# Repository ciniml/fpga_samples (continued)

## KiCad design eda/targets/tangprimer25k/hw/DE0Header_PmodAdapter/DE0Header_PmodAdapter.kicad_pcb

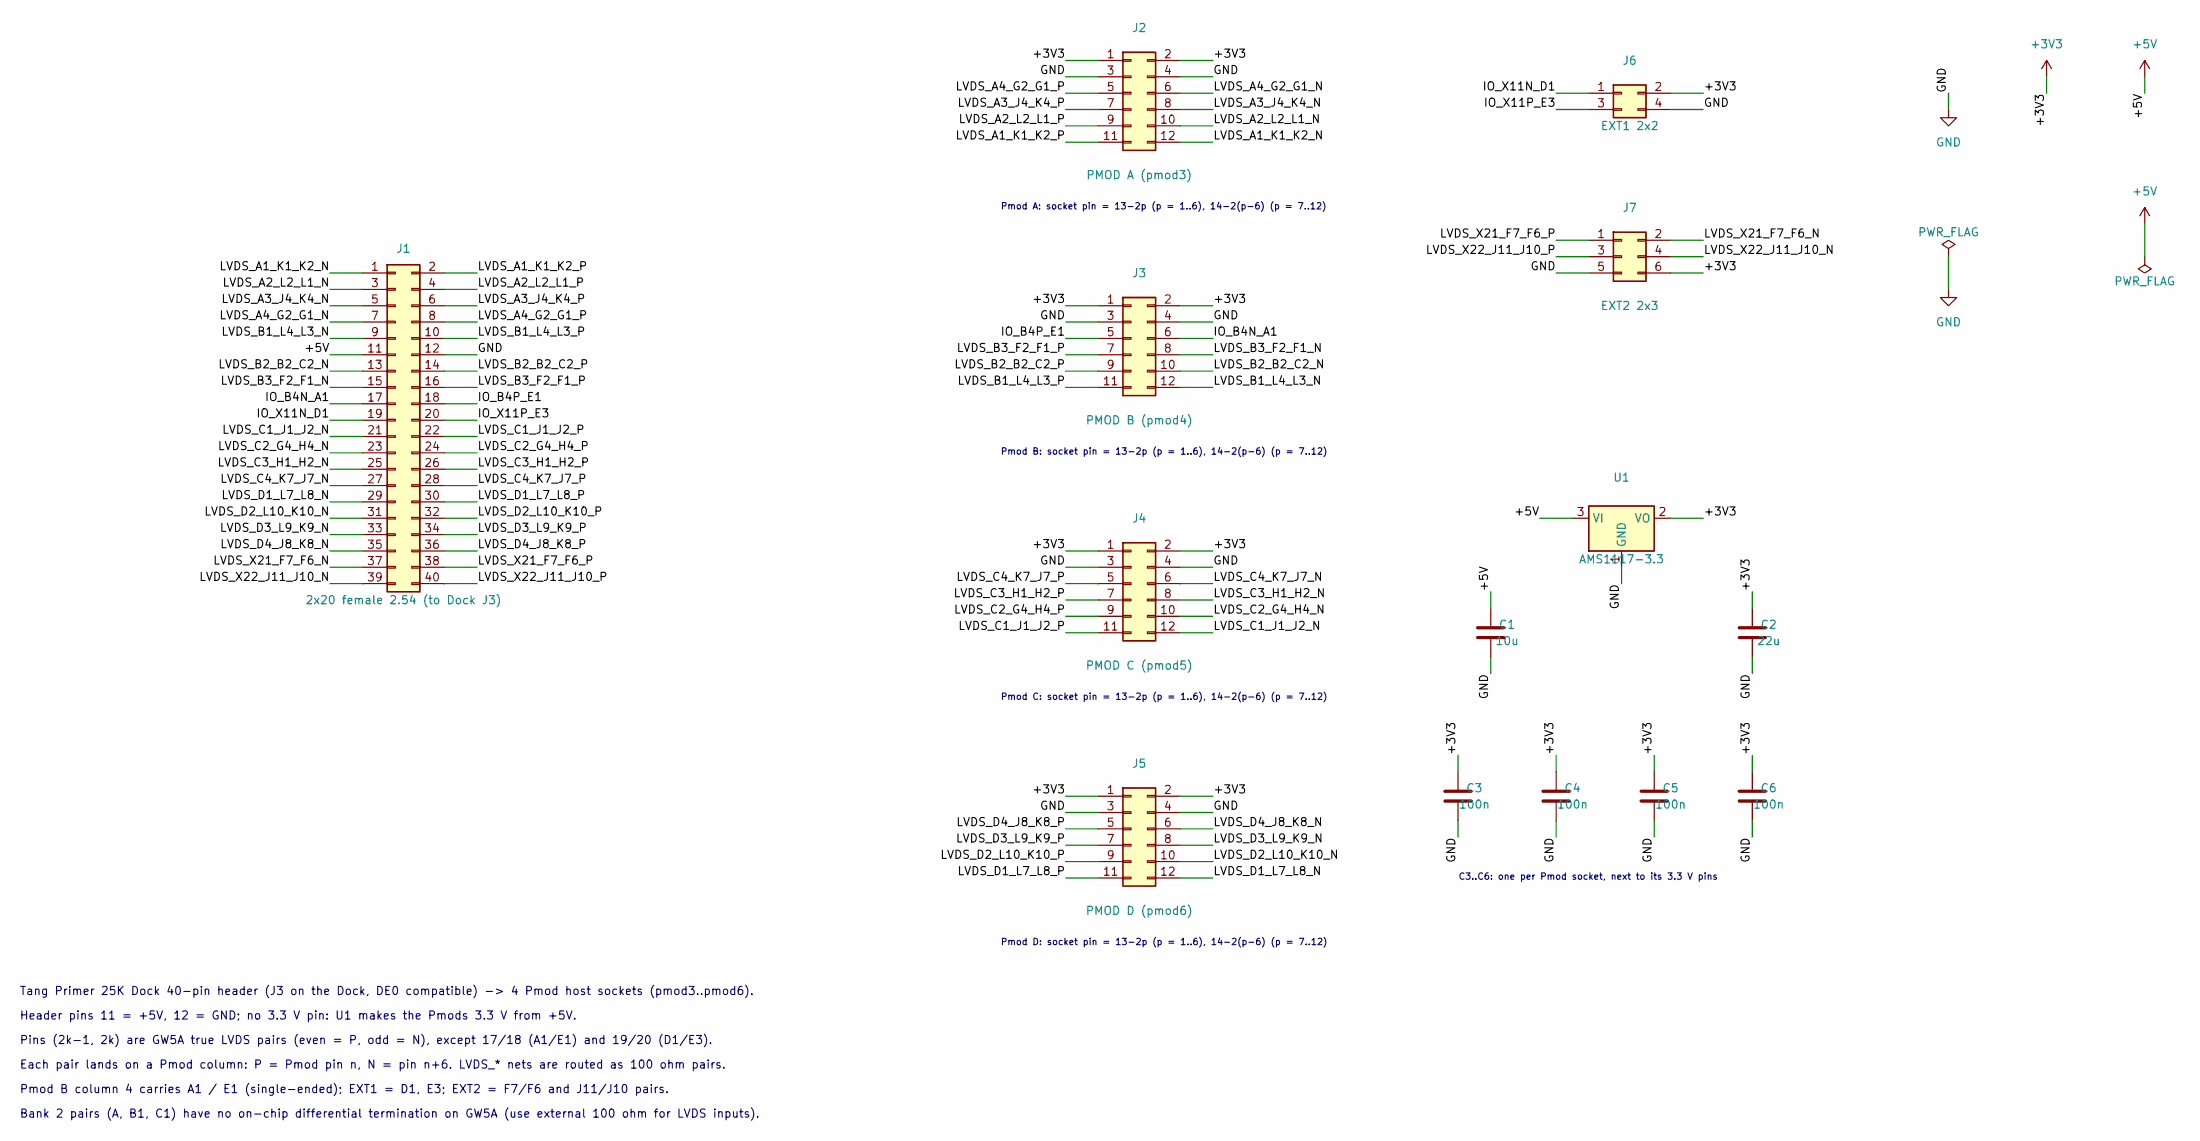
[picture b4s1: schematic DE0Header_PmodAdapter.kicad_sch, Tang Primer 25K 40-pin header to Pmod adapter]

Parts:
C1: 10u; C_0805_2012Metric; MPN Samsung CL21A106KAYNNNE; LCSC C15850
C2: 22u; C_0805_2012Metric; MPN Samsung CL21A226MAQNNNE; LCSC C45783
C3, C4, C5, C6: 100n; C_0402_1005Metric; MPN Samsung CL05B104KO5NNNC; LCSC C1525
J1: 2x20 female 2.54 (to Dock J3); PinSocket_2x20_P2.54mm_Vertical; MPN BOOMELE 2.54-2*20P; LCSC C5124634
J2: PMOD A (pmod3); PinSocket_2x06_P2.54mm_Horizontal; MPN Hong Cheng HC-PM254-8.5H-2x6PW; LCSC C22373932
J3: PMOD B (pmod4); PinSocket_2x06_P2.54mm_Horizontal; MPN Hong Cheng HC-PM254-8.5H-2x6PW; LCSC C22373932
J4: PMOD C (pmod5); PinSocket_2x06_P2.54mm_Horizontal; MPN Hong Cheng HC-PM254-8.5H-2x6PW; LCSC C22373932
J5: PMOD D (pmod6); PinSocket_2x06_P2.54mm_Horizontal; MPN Hong Cheng HC-PM254-8.5H-2x6PW; LCSC C22373932
J6: EXT1 2x2; PinHeader_2x02_P2.54mm_Vertical; MPN BOOMELE 2.54-2*2PPin; LCSC C66690
J7: EXT2 2x3; PinHeader_2x03_P2.54mm_Vertical; MPN BOOMELE 2.54-2*3PPin; LCSC C65114
U1: AMS1117-3.3; SOT-223-3_TabPin2; MPN AMS AMS1117-3.3; LCSC C6186

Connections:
+3V3: C2.1, C3.1, C4.1, C5.1, C6.1, J2.1, J2.2, J3.1, J3.2, J4.1, J4.2, J5.1, J5.2, J6.2, J7.6, U1.2 (VO)
+5V: C1.1, J1.11, U1.3 (VI)
/IO_B4N_A1: J1.17, J3.6
/IO_B4P_E1: J1.18, J3.5
/IO_X11N_D1: J1.19, J6.1
/IO_X11P_E3: J1.20, J6.3
/LVDS_A1_K1_K2_N: J1.1, J2.12
/LVDS_A1_K1_K2_P: J1.2, J2.11
/LVDS_A2_L2_L1_N: J1.3, J2.10
/LVDS_A2_L2_L1_P: J1.4, J2.9
/LVDS_A3_J4_K4_N: J1.5, J2.8
/LVDS_A3_J4_K4_P: J1.6, J2.7
/LVDS_A4_G2_G1_N: J1.7, J2.6
/LVDS_A4_G2_G1_P: J1.8, J2.5
/LVDS_B1_L4_L3_N: J1.9, J3.12
/LVDS_B1_L4_L3_P: J1.10, J3.11
/LVDS_B2_B2_C2_N: J1.13, J3.10
/LVDS_B2_B2_C2_P: J1.14, J3.9
/LVDS_B3_F2_F1_N: J1.15, J3.8
/LVDS_B3_F2_F1_P: J1.16, J3.7
/LVDS_C1_J1_J2_N: J1.21, J4.12
/LVDS_C1_J1_J2_P: J1.22, J4.11
/LVDS_C2_G4_H4_N: J1.23, J4.10
/LVDS_C2_G4_H4_P: J1.24, J4.9
/LVDS_C3_H1_H2_N: J1.25, J4.8
/LVDS_C3_H1_H2_P: J1.26, J4.7
/LVDS_C4_K7_J7_N: J1.27, J4.6
/LVDS_C4_K7_J7_P: J1.28, J4.5
/LVDS_D1_L7_L8_N: J1.29, J5.12
/LVDS_D1_L7_L8_P: J1.30, J5.11
/LVDS_D2_L10_K10_N: J1.31, J5.10
/LVDS_D2_L10_K10_P: J1.32, J5.9
/LVDS_D3_L9_K9_N: J1.33, J5.8
/LVDS_D3_L9_K9_P: J1.34, J5.7
/LVDS_D4_J8_K8_N: J1.35, J5.6
/LVDS_D4_J8_K8_P: J1.36, J5.5
/LVDS_X21_F7_F6_N: J1.37, J7.2
/LVDS_X21_F7_F6_P: J1.38, J7.1
/LVDS_X22_J11_J10_N: J1.39, J7.4
/LVDS_X22_J11_J10_P: J1.40, J7.3
GND: C1.2, C2.2, C3.2, C4.2, C5.2, C6.2, J1.12, J2.3, J2.4, J3.3, J3.4, J4.3, J4.4, J5.3, J5.4, J6.4, J7.5, U1.1 (GND)

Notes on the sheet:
Pmod A: socket pin = 13-2p (p = 1..6), 14-2(p-6) (p = 7..12)
Pmod B: socket pin = 13-2p (p = 1..6), 14-2(p-6) (p = 7..12)
Pmod C: socket pin = 13-2p (p = 1..6), 14-2(p-6) (p = 7..12)
Pmod D: socket pin = 13-2p (p = 1..6), 14-2(p-6) (p = 7..12)
C3..C6: one per Pmod socket, next to its 3.3 V pins
Tang Primer 25K Dock 40-pin header (J3 on the Dock, DE0 compatible) -> 4 Pmod host sockets (pmod3..pmod6).
Header pins 11 = +5V, 12 = GND; no 3.3 V pin: U1 makes the Pmods 3.3 V from +5V.
Pins (2k-1, 2k) are GW5A true LVDS pairs (even = P, odd = N), except 17/18 (A1/E1) and 19/20 (D1/E3).
Each pair lands on a Pmod column: P = Pmod pin n, N = pin n+6. LVDS_* nets are routed as 100 ohm pairs.
Pmod B column 4 carries A1 / E1 (single-ended); EXT1 = D1, E3; EXT2 = F7/F6 and J11/J10 pairs.
Bank 2 pairs (A, B1, C1) have no on-chip differential termination on GW5A (use external 100 ohm for LVDS inputs).

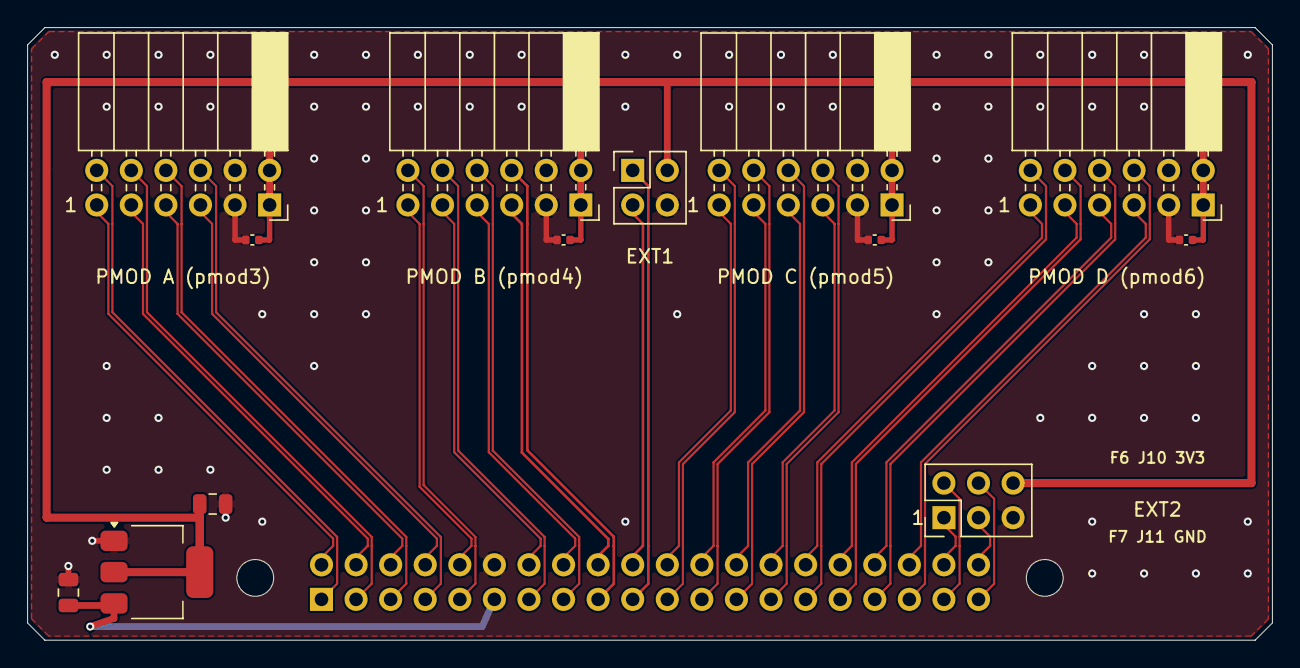
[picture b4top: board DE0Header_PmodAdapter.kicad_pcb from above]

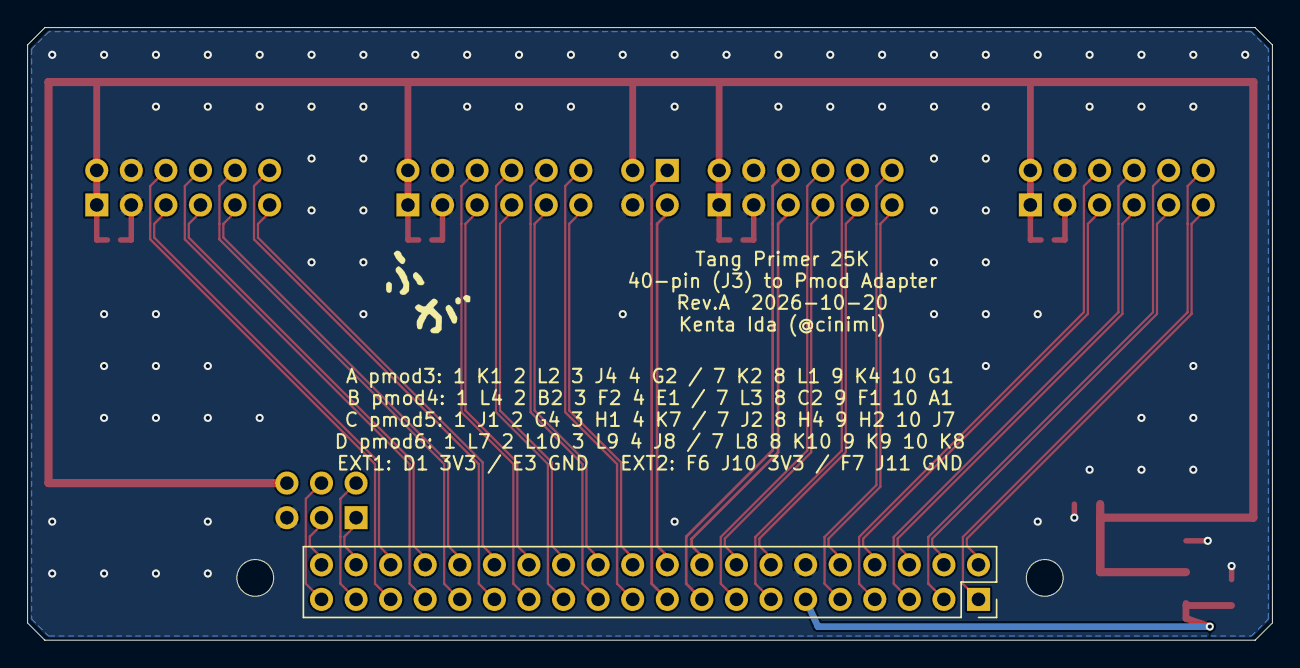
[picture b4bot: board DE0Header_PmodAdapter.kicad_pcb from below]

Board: 2 copper layers, 91.4 x 45.0 mm, 17 parts (2 on the bottom side), 41 nets.

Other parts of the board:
H1, H2: MountingHole_2.7mm_M2.5_ISO7380
LOGO1: logo

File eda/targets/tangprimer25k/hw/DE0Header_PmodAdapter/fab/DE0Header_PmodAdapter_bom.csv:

"Reference","Value","Footprint","QUANTITY","LCSC","MPN","Description"
"C1","10u","Capacitor_SMD:C_0805_2012Metric","1","C15850","Samsung CL21A106KAYNNNE","10 uF 25 V X5R 0805 (LDO input)"
"C2","22u","Capacitor_SMD:C_0805_2012Metric","1","C45783","Samsung CL21A226MAQNNNE","22 uF 25 V X5R 0805 (LDO output)"
"C3,C4,C5,C6","100n","Capacitor_SMD:C_0402_1005Metric","4","C1525","Samsung CL05B104KO5NNNC","100 nF 16 V X7R 0402 (Pmod 3.3 V)"
"J1","2x20 female 2.54 (to Dock J3)","Connector_PinSocket_2.54mm:PinSocket_2x20_P2.54mm_Vertical","1","C5124634","BOOMELE 2.54-2*20P","2x20 2.54 mm female socket, 8.5 mm, mounted on the bottom side"
"J2","PMOD A (pmod3)","Connector_PinSocket_2.54mm:PinSocket_2x06_P2.54mm_Horizontal","1","C22373932","Hong Cheng HC-PM254-8.5H-2x6PW","Pmod host: 2x6 2.54 mm right-angle female socket"
"J3","PMOD B (pmod4)","Connector_PinSocket_2.54mm:PinSocket_2x06_P2.54mm_Horizontal","1","C22373932","Hong Cheng HC-PM254-8.5H-2x6PW","Pmod host: 2x6 2.54 mm right-angle female socket"
"J4","PMOD C (pmod5)","Connector_PinSocket_2.54mm:PinSocket_2x06_P2.54mm_Horizontal","1","C22373932","Hong Cheng HC-PM254-8.5H-2x6PW","Pmod host: 2x6 2.54 mm right-angle female socket"
"J5","PMOD D (pmod6)","Connector_PinSocket_2.54mm:PinSocket_2x06_P2.54mm_Horizontal","1","C22373932","Hong Cheng HC-PM254-8.5H-2x6PW","Pmod host: 2x6 2.54 mm right-angle female socket"
"J6","EXT1 2x2","Connector_PinHeader_2.54mm:PinHeader_2x02_P2.54mm_Vertical","1","C66690","BOOMELE 2.54-2*2PPin","2x2 2.54 mm pin header"
"J7","EXT2 2x3","Connector_PinHeader_2.54mm:PinHeader_2x03_P2.54mm_Vertical","1","C65114","BOOMELE 2.54-2*3PPin","2x3 2.54 mm pin header"
"U1","AMS1117-3.3","Package_TO_SOT_SMD:SOT-223-3_TabPin2","1","C6186","AMS AMS1117-3.3","3.3 V 1 A LDO (5 V from the header pin 11)"

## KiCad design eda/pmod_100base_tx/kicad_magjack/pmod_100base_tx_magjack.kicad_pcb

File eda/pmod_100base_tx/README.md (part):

# Pmod 100BASE-TX 直結 PHY 基板 — 設計検討

外付け PHY チップを使わず、Tang Primer 25K (GW5A-25) の I/O だけで 100BASE-TX を送受信するための
Pmod 基板案。**パルストランスも使わず**、コンデンサ結合 (transformerless) で RJ45 に直結する。
受信は EasyCDR / USB HS と同じブラインド・オーバーサンプリング CDR (`rtl/oscdr` の `OsCdr`)。
RTL は `rtl/eth100_phy` (Veryl)。

状態: **机上検討 + RTL シミュレーション合格 + 実機用ビットストリーム生成済み** (KiCad 10 データ: トランスレス版 `kicad/`、MagJack 版 `kicad_magjack/`。実機未検証)。

## 1. 要求と方針

| 項目 | 内容 |
|---|---|
| 規格 | 100BASE-TX (4B5B + 11bit スクランブラ + MLT-3、125 Mbaud)。全二重。10BASE-T は非対象 (FLP の送受信のみ) |
| 役割 | MDI (NIC 側): **TX = RJ45 1/2、RX = 3/6**。相手はスイッチ / Auto-MDIX の PC |
| 絶縁 | トランスレス版はなし (**相手側にトランスがある前提**、PoE 非対応)。MagJack 版 (§3.5) は 1500V 絶縁 |
| オートネゴ | FLP を自前生成 / 復号し 100BASE-TX FD を広告。出さないと相手はパラレル検出で **100M 半二重**に落ちる |
| Pmod | **1 ポート** (信号 8 本 = 差動対 4)。3.3V バンク。Tang Primer 25K の csv `pmod0` を想定 |
| ケーブル | まず数 m。イコライザなしの 2 値コンパレータなので 100m は保証しない (§6) |

## 2. 原理

### 2.1 MLT-3 を比較器 2 個で受ける

差動受信電圧 `v` (+1/0/−1 V 名目) を、しきい値 `+th` と `−th` の 2 つの LVDS 入力 (比較器) で判定する。

| レベル | A = (v > +th) | B = (v > −th) | c = A ^ B |
|---|---|---|---|
| +1 | 1 | 1 | 0 |
| 0 | 0 | 1 | 1 |
| −1 | 0 | 0 | 0 |

MLT-3 はスクランブル後のビット 1 ごとに 0→+→0→−→0 と 1 段動くので、**どの遷移でも A か B の
どちらか一方だけが反転する**。よって `c = A ^ B` (= |v| < th の窓比較) は **NRZI 波形そのもの**になり、
`c[n] ^ c[n−1]` がスクランブル後のビット。CDR はこの `c` 1 本に対して OsCdr を回せばよい
(A/B はサンプル単位で XOR してから OsCdr に入れる)。A/B 個別のサンプルはアイスキャン・FLP 検出に使う。

### 2.2 サンプリング

- IDES4 ×2 (A, B)、FCLK 250 MHz DDR / PCLK 125 MHz = **500 MS/s、4 サンプル/シンボル**
  (EasyCDR 1 Gbps と同じ OSR=4。USB HS の OSIDES32 3.84 GS/s よりずっと楽)
- OsCdr `SAMPLES=4, OSR=4, IIR=4, FRAC=4, HYST=16`: 1 ワード = 1 シンボル、`nbits` は 0/1/2
  (プレシオクロナスのスリップ吸収)
- 送信もシンボルクロック 125 MHz。送受信とも同じ 125 MHz ドメインで、受信側の周波数差は
  「1 クロックに 0〜2 ビット」として PCS が吸収する (FIFO 不要)
- **8 サンプル/シンボル (1 GS/s, OSR=8) は不可**: OsCdr の追従判定は「データ点の隣のクラス (d, d+2) に
  エッジが来たら 1 ステップ」で OSR=4 前提。OSR=8 ではエッジが d±4 にあり、アイがほぼ閉じるまで動かない
  (USB HS はパケット毎の再捕捉で回避していた)。シミュレーションで ±200 ppm でも片方向が全滅した
- **OsCdr に `FRAC` (小数ビット) を追加**: 1 ワード 1 シンボルだとエッジは高々 1 個/ワードで、
  整数の IIR 減衰 `acc >> IIR` が 0 に丸められ全クラスが飽和する。`FRAC=0` (既定) は従来と同一論理で、
  既存 oscdr テスト 17 本は通過

## 3. 回路

### 3.1 ブロック図

```
 RJ45 (磁気なし)                    Pmod 基板                                         FPGA (Pmod)
                                                    ┌─ Rs 62Ω ─ TX_P ──────────────── pin4  LVCMOS33 DRIVE=16
 1 TD+ ──┬─ TVS ── C 0.1µF/100V ──┬─ Cr 47pF ─┤     ├─ Rp 120Ω ─ GND
 2 TD− ──┼─ TVS ── C 0.1µF/100V ──┼─ Cr 47pF ─┤     ├─ Rs 62Ω ─ TX_N ──────────────── pin10 LVCMOS33 DRIVE=16
         │                     (CMC 任意, 0Ω 実装)   └─ Rp 120Ω ─ GND

 3 RD+ ──┬─ TVS ──┬─ 49.9Ω ─┬─ 49.9Ω ─┬─ RD−                      (100Ω 終端、中点 Ct 10nF/100V → GND)
 6 RD− ──┘        │         Ct        │
                  ├─ Ca 0.1µF ── A_P ──┬─ Rb 2.2k ─ VB ────────── pin1  比較器 A  P
                  │                                         ┌──── pin7          A  N
                  │             RD− ── Ca 0.1µF ── A_N ─────┴─ Rb 2.2k ─ VTH_A
                  ├─ Ca 0.1µF ── B_P ──┬─ Rb 2.2k ─ VTH_B ──── pin2  比較器 B  P
                                RD− ── Ca 0.1µF ── B_N ──┬─ Rb 2.2k ─ VB ──── pin8  B  N

 VB    = 3.3V ─ 270Ω ─┬─ 180Ω ─ GND   (1.32V、10µF + 0.1µF)
 VTH_A = PWM_A(pin3) ─ 3.3k ─┬─ 1k ─ VB    (1µF → GND)
 VTH_B = PWM_B(pin9) ─ 3.3k ─┬─ 1k ─ VB    (1µF → GND)
 4/5, 7/8 (未使用対): 各対を 75Ω ×2 で中点 → 1nF/2kV → GND (Bob Smith 相当、任意)
```

### 3.2 受信: しきい値

- 比較器 A: `A_P = VB + v+`、`A_N = VTH_A + v−` → **A = 1 ⇔ v > (VTH_A − VB)**
- 比較器 B: `B_P = VTH_B + v+`、`B_N = VB + v−` → **B = 1 ⇔ v > −(VTH_B − VB)**
- つまり 2 本の PWM はどちらも「VB より上」に置けば ±th になる。名目 `VTH_A = VTH_B = VB + 0.5V` (短ケーブル)
- PWM → しきい値: `VTH − VB = (D × 3.3V − VB) × 1k / 4.3k` = **−0.31 V (D=0) 〜 +0.46 V (D=1)**。
  10bit PWM (125 MHz / 1024 = 122 kHz) で ~0.75 mV/LSB、RC τ ≈ 0.77 ms
  - 0.5V に少し届かないが、受信端で 1V 振幅が残るのは極短ケーブルのみ。長くするほど最適点は下がる。
    上を広げたいときは 3.3k → 2.7k
- 2 本独立なので、**差 (VTH_A − VTH_B) でベースラインの補正**、**和でしきい値の大きさ**を動かせる。
  さらに CDR を凍結したまま掃引すれば振幅方向のアイスキャンになる (OsCdr の位相固定と組み合わせて 2 次元)
- 各比較器入力は 0.1µF + 2.2k の HPF (720 Hz)。終端 (100Ω) とは別ノードにして DC オフセットを個別に与える。
  2.2k ×4 のタップ負荷は終端に対して無視できる
- 内蔵終端は使わない (`DIFF_RESISTOR=OFF`)。LVDS25 入力の電圧範囲は VB±1V ≒ 0.3〜2.3V
- ベースラインワンダ: 主因は**相手側トランスの低域遮断** (~20 kHz) で、こちらのコンデンサの有無に関係なく来る。
  通常のスクランブル済みデータなら数十 mV 程度で、±0.5V のしきい値に対して余裕がある。
  意図的な killer packet には弱い (§6)

### 3.3 送信: LVCMOS33 2 本で 3 値

| TX_P | TX_N | 出力 |
|---|---|---|
| 1 | 0 | +1 V |
| 0 | 1 | −1 V |
| 0 | 0 | 0 |

- 片側のテブナン等価を **2V / 50Ω** にすると 100Ω 負荷で ±1V。ピン出力抵抗を ~20Ω (DRIVE=16) と見て
  Rs = 62Ω (+20Ω)、Rp = 120Ω: V_th = 3.3 × 120/202 = 1.96V、R_th = 48.7Ω → **差動 0.99V**。
  規格は 0.95〜1.05V なので実測で Rs を合わせる (USB HS も DRIVE で振幅が大きく変わった)
- 立ち上がり 3〜5 ns (規格): ノードのインピーダンス ~25Ω (50Ω ‖ 線路 50Ω) に Cr ≈ 47pF で ~2.6 ns。
  スコープで合わせる
- 2 本で作るので**同相電圧が 0 ↔ 1V で段差状に動く** (±レベル時のみ片方が H)。直列コンデンサの後は過渡分だけが
  ケーブルに乗り、相手のトランスとコモンモードチョークで落ちる。EMI 対策に CMC (例: 0805 の 90Ω 級) の
  フットプリントを用意し、初版は 0Ω 実装
- 消費: H 側ピン ~16 mA。平均 1 本未満
- FLP (オートネゴのリンクパルス) も同じ回路で +1V × 100ns を出す。10BASE-T の規格振幅 (2.2〜2.8V) より小さいが、
  相手の受信スケルチ (~0.3〜0.6V) は超える見込み (§6 リスク)

### 3.4 保護・PoE (トランスレス版)

- RJ45 直近に 4 ライン低容量 TVS アレイ (TX 2 + RX 2)。**双方向品** (TPD4E02B04): 線路側に DC の基準が無いので、
  単方向品だと受信 FLP の負側で整流が起きる
- 線路側ノード (TD±, RD±) は直列 C と TVS のリークでしか DC が決まらないので、**1 MΩ の放電抵抗**で GND に落とす
- **PoE 非対応**。当初「線路側 C を 100V 耐圧にすればパッシブ PoE (24〜57V の同相電圧) に耐える」としていたが誤り:
  ≤1 pF 級 TVS は数 V でクランプするため導通・破損する。IEEE PoE (802.3af/at) は 25kΩ シグネチャ検出が
  通らないので給電されないが、パッシブ PoE のポートには**つながない** (シルクに明記)
- **相手機器もトランスレスの場合**は GND 電位差がそのまま乗る → 対象外

### 3.5 MagJack 版 (`kicad_magjack/`)

トランスレス版の不安要素 (PoE、線路側の DC 浮き、同相段差、相手もトランスレスのとき) をまとめて消す実用版。
FPGA 側の回路・ピン割り当て・RTL は共通で、RJ45 周りだけが違う。トランスは 1:1 なので FLP 振幅 (1V) と
ベースラインワンダ (主因は相手側トランス) は変わらない。

```
 Pmod ── Rs/Rp/Cr ── C (DC 阻止、必須) ── TD± ┐            ┌─ RJ45 1/2
                                               ├ HR911105A ┤  (1:1 + CT、CMC、Bob Smith 内蔵)
 Pmod ── 比較器タップ ── 100Ω 終端 ────── RD± ┘            └─ RJ45 3/6
 TCT / RCT (PHY 側センタータップ) ── 0.1µF ── GND   (3.3V に吊らない: 送信は電圧駆動)
 低容量 TVS (双方向 TPD4E02B04) は PHY 側 (トランスと回路の間)
```

- **TX の直列 C は必須**: 2 本で 3 値を作るので ± 状態では TX_P/TX_N 間に DC が掛かる。巻線の DCR は ~1Ω で、
  C が無いと抵抗網経由の DC 電流で磁気飽和する。絶縁側なので耐圧は 16〜50V でよい
- センタータップは AC 接地のみ。電流出力型 PHY 用のリファレンス回路 (CT を電源へ) は流用しない。
  そのため PHY 側も DC 的には浮いている (CT も終端中点もコンデンサ経由) → TVS は双方向品。
  DC を固定したければ TCT/RCT → GND に 1 MΩ (未実装)
- 基板: 2 層 20.32 × 52.0 mm、HR911105A (KiCad 10 stock の `RJ45_Hanrun_HR911105A_Horizontal`)。
  ピン 1 TD+ / 2 TD− / 3 RD+ / 4 TCT / 5 RCT / 6 RD− / 8 内蔵 Bob Smith → GND、LED 未使用。
  開口の向きと内蔵 1000pF の耐圧はデータシートで要確認 (stock に 3D モデルなし)
- PoE: 給電機器 (PSE) ではない。パッシブ PoE の同相電圧はトランスのセンタータップと内蔵 Bob Smith 側で受け、
  回路側は絶縁される

#### JLCPCB 実装用の部品 (LCSC 在庫・単価は 2026-10-19 時点)

`kicad_magjack/tools/outputs.sh` が `out/jlc/` に gerber zip、BOM、CPL を出す (CPL は gerber と同じ絶対座標)。
部品は `tools/design.py` の `lcsc` が正。値・MPN だけ変えるときは `gen_sch.py` → `update_fields.py`
(配線を残したまま PCB のフィールドだけ更新。`gen_pcb.py` は配線が消える)。

| Ref | 部品 | LCSC | JLC 区分 | 備考 |
|---|---|---|---|---|
| R1, R2 (Rs) | 62Ω 1% 0402 FOJAN FRC0402F62R0TS | C2909376 | Extended | 62Ω は Basic に無い。実機で振幅合わせに交換する前提 |
| R3, R4 | 120Ω 1% 0402 | C25079 | Basic | |
| R7, R8 | 49.9Ω 1% 0402 | C25120 | Basic | |
| R9–R12 | 2.2kΩ 1% 0402 | C25879 | Basic | |
| R13 / R14 (VB) | **330Ω / 220Ω** 1% 0402 | C25104 / C25091 | Basic | トランスレス版の 270/180 は両方 Extended なので変更。同じ 1.32V、出力抵抗 132Ω、5.9mA |
| R15, R17 | 3.3kΩ 1% 0402 | C25890 | Basic | 2.7k (C25885、Extended) でしきい値範囲が広がる |
| R16, R18 | 1kΩ 1% 0402 | C11702 | Basic | |
| C1, C2 (Cr) | 47pF C0G 50V 0402 | C1567 | Basic | |
| C3, C4, C6–C9 | 0.1µF X7R 50V 0603 | C14663 | Basic | TX DC 阻止 / Ca タップ |
| C5 | 10nF X7R 50V 0402 | C15195 | Basic | |
| C10, C14 | 10µF X5R 10V 0603 | C19702 | Basic | |
| C11, C15–C18 | 0.1µF X7R 50V 0402 | C307331 | Basic | C1525 (16V) は LCSC 在庫 0 だったため |
| C12, C13 | 1µF X5R 25V 0402 | C52923 | Basic | |
| U1 | TI TPD4E02B04DQAR (USON-10) | C106794 | Extended | 在庫 3.7 万。互換品 TECH PUBLIC TPD4E02B04DQAR-TP (C2841426) は容量の規定が違うので使わない |
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
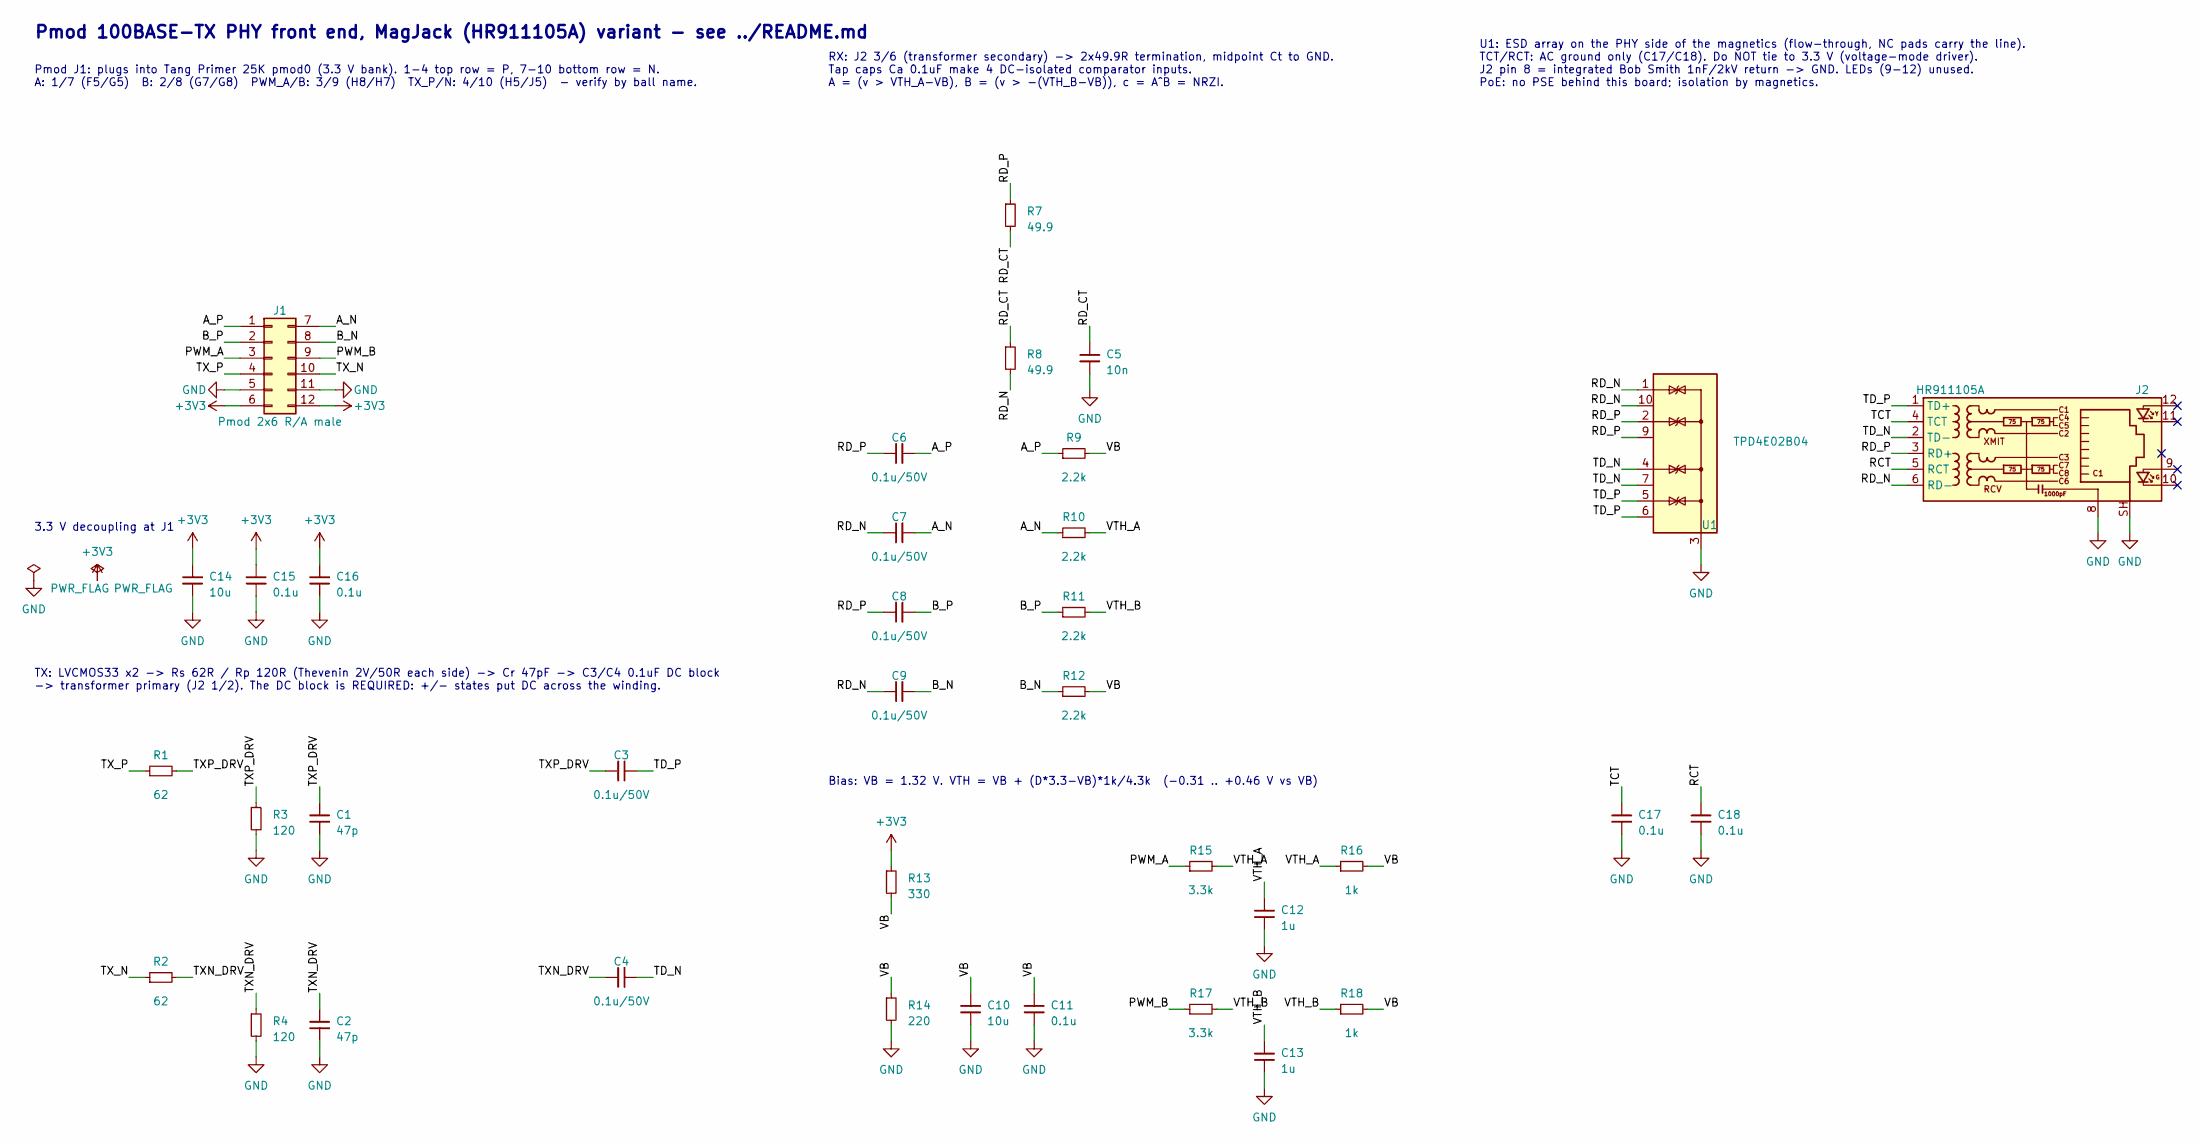
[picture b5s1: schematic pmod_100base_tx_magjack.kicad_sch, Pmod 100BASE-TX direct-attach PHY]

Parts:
C1, C2: 47p; C_0402_1005Metric; MPN 0402CG470J500NT; LCSC C1567
C3, C4, C6, C7, C8, C9: 0.1u/50V; C_0603_1608Metric; MPN CC0603KRX7R9BB104; LCSC C14663
C5: 10n; C_0402_1005Metric; MPN CL05B103KB5NNNC; LCSC C15195
C10, C14: 10u; C_0603_1608Metric; MPN CL10A106KP8NNNC; LCSC C19702
C11, C15, C16, C17, C18: 0.1u; C_0402_1005Metric; MPN CL05B104KB54PNC; LCSC C307331
C12, C13: 1u; C_0402_1005Metric; MPN CL05A105KA5NQNC; LCSC C52923
J1: Pmod 2x6 R/A male; Pmod_Peripheral_2x06_P2.54mm_Horizontal; MPN TSW-106-08-G-D-RA
J2: HR911105A; RJ45_Hanrun_HR911105A_Horizontal; MPN HR911105A; LCSC C12074
R1, R2: 62; R_0402_1005Metric; MPN FRC0402F62R0TS; LCSC C2909376
R3, R4: 120; R_0402_1005Metric; MPN 0402WGF1200TCE; LCSC C25079
R7, R8: 49.9; R_0402_1005Metric; MPN 0402WGF499JTCE; LCSC C25120
R9, R10, R11, R12: 2.2k; R_0402_1005Metric; MPN 0402WGF2201TCE; LCSC C25879
R13: 330; R_0402_1005Metric; MPN 0402WGF3300TCE; LCSC C25104
R14: 220; R_0402_1005Metric; MPN 0402WGF2200TCE; LCSC C25091
R15, R17: 3.3k; R_0402_1005Metric; MPN 0402WGF3301TCE; LCSC C25890
R16, R18: 1k; R_0402_1005Metric; MPN 0402WGF1001TCE; LCSC C11702
U1: TPD4E02B04; USON-10_2.5x1.0mm_P0.5mm; MPN TPD4E02B04DQAR; LCSC C106794

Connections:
+3V3: C14.1, C15.1, C16.1, J1.6, J1.12, R13.1
/A_N: C7.2, J1.7, R10.1
/A_P: C6.2, J1.1, R9.1
/B_N: C9.2, J1.8, R12.1
/B_P: C8.2, J1.2, R11.1
/PWM_A: J1.3, R15.1
/PWM_B: J1.9, R17.1
/RCT: C18.1, J2.5 (RCT)
/RD_CT: C5.1, R7.2, R8.1
/RD_N: C7.1, C9.1, J2.6 (RD-), R8.2, U1.1 (IO1), U1.10 (NC)
/RD_P: C6.1, C8.1, J2.3 (RD+), R7.1, U1.2 (IO2), U1.9 (NC)
/TCT: C17.1, J2.4 (TCT)
/TD_N: C4.2, J2.2 (TD-), U1.4 (IO3), U1.7 (NC)
/TD_P: C3.2, J2.1 (TD+), U1.5 (IO4), U1.6 (NC)
/TXN_DRV: C2.1, C4.1, R2.2, R4.1
/TXP_DRV: C1.1, C3.1, R1.2, R3.1
/TX_N: J1.10, R2.1
/TX_P: J1.4, R1.1
/VB: C10.1, C11.1, R9.2, R12.2, R13.2, R14.1, R16.2, R18.2
/VTH_A: C12.1, R10.2, R15.2, R16.1
/VTH_B: C13.1, R11.2, R17.2, R18.1
GND: C1.2, C2.2, C5.2, C10.2, C11.2, C12.2, C13.2, C14.2, C15.2, C16.2, C17.2, C18.2, J1.5, J1.11, J2.8, J2.SH, R3.2, R4.2, R14.2, U1.3 (G), U1.8 (G)

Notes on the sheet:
Pmod 100BASE-TX PHY front end, MagJack (HR911105A) variant - see ../README.md
Pmod J1: plugs into Tang Primer 25K pmod0 (3.3 V bank). 1-4 top row = P, 7-10 bottom row = N. A: 1/7 (F5/G5) B: 2/8 (G7/G8) PWM_A/B: 3/9 (H8/H7) TX_P/N: 4/10 (H5/J5) - verify by ball name.
TX: LVCMOS33 x2 -> Rs 62R / Rp 120R (Thevenin 2V/50R each side) -> Cr 47pF -> C3/C4 0.1uF DC block -> transformer primary (J2 1/2). The DC block is REQUIRED: +/- states put DC across the winding.
RX: J2 3/6 (transformer secondary) -> 2x49.9R termination, midpoint Ct to GND. Tap caps Ca 0.1uF make 4 DC-isolated comparator inputs. A = (v > VTH_A-VB), B = (v > -(VTH_B-VB)), c = A^B = NRZI.
Bias: VB = 1.32 V. VTH = VB + (D*3.3-VB)*1k/4.3k (-0.31 .. +0.46 V vs VB)
U1: ESD array on the PHY side of the magnetics (flow-through, NC pads carry the line). TCT/RCT: AC ground only (C17/C18). Do NOT tie to 3.3 V (voltage-mode driver). J2 pin 8 = integrated Bob Smith 1nF/2kV return -> GND. LEDs (9-12) unused. PoE: no PSE behind this board; isolation by magnetics.
3.3 V decoupling at J1

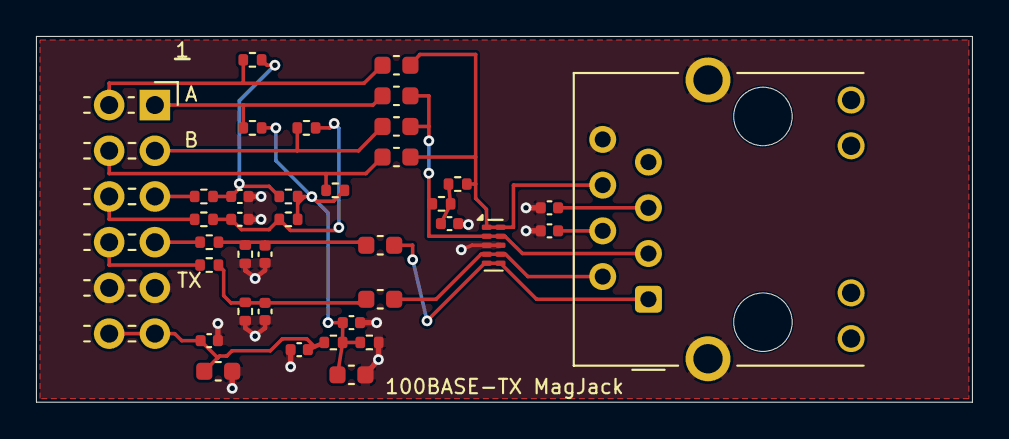
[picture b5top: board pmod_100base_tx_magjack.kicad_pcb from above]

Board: 2 copper layers, 52.0 x 20.3 mm, 38 parts (1 on the bottom side), 22 nets.

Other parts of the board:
LOGO1: Logo_Open_Hardware_Small; logo

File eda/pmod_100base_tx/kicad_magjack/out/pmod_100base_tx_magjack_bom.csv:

"Refs","Value","Footprint","MPN","Manufacturer","LCSC","Description","Qty","DNP"
"C1,C2","47p","Capacitor_SMD:C_0402_1005Metric","0402CG470J500NT","FH","C1567","Cr C0G 50V, edge rate tune","2",""
"C3,C4,C6-C9","0.1u/50V","Capacitor_SMD:C_0603_1608Metric","CC0603KRX7R9BB104","Yageo","C14663","Ca tap, X7R 50V,TX DC block (no DC across the winding)","6",""
"C5","10n","Capacitor_SMD:C_0402_1005Metric","CL05B103KB5NNNC","Samsung","C15195","Ct termination midpoint, X7R 50V","1",""
"C10,C14","10u","Capacitor_SMD:C_0603_1608Metric","CL10A106KP8NNNC","Samsung","C19702","X5R 10V","2",""
"C11,C15-C18","0.1u","Capacitor_SMD:C_0402_1005Metric","CL05B104KB54PNC","Samsung","C307331","RX centre tap AC ground (NOT to 3.3 V),TX centre tap AC ground (NOT to 3.3 V),X7R 50V","5",""
"C12,C13","1u","Capacitor_SMD:C_0402_1005Metric","CL05A105KA5NQNC","Samsung","C52923","X5R 25V","2",""
"J1","Pmod 2x6 R/A male","pmod_100base_tx:Pmod_Peripheral_2x06_P2.54mm_Horizontal","TSW-106-08-G-D-RA","Samtec","","Pmod peripheral plug, 2x6 2.54mm right angle male, Type 1-6 top / 7-12 bottom","1",""
"J2","HR911105A","Connector_RJ:RJ45_Hanrun_HR911105A_Horizontal","HR911105A","HanRun","C12074","RJ45 MagJack 10/100, 1:1 magnetics with CT, Bob Smith 75R+1nF/2kV integrated (pin 8), LEDs unused","1",""
"R1,R2","62","Resistor_SMD:R_0402_1005Metric","FRC0402F62R0TS","FOJAN","C2909376","Rs, tune for 0.95-1.05 V diff","2",""
"R3,R4","120","Resistor_SMD:R_0402_1005Metric","0402WGF1200TCE","UNI-ROYAL","C25079","Rp","2",""
"R7,R8","49.9","Resistor_SMD:R_0402_1005Metric","0402WGF499JTCE","UNI-ROYAL","C25120","RX termination","2",""
"R9-R12","2.2k","Resistor_SMD:R_0402_1005Metric","0402WGF2201TCE","UNI-ROYAL","C25879","Rb","4",""
"R13","330","Resistor_SMD:R_0402_1005Metric","0402WGF3300TCE","UNI-ROYAL","C25104","VB divider (1.32 V)","1",""
"R14","220","Resistor_SMD:R_0402_1005Metric","0402WGF2200TCE","UNI-ROYAL","C25091","VB divider","1",""
"R15,R17","3.3k","Resistor_SMD:R_0402_1005Metric","0402WGF3301TCE","UNI-ROYAL","C25890","PWM filter (2.7k widens range)","2",""
"R16,R18","1k","Resistor_SMD:R_0402_1005Metric","0402WGF1001TCE","UNI-ROYAL","C11702","PWM filter","2",""
"U1","TPD4E02B04","Package_SON:USON-10_2.5x1.0mm_P0.5mm","TPD4E02B04DQAR","Texas Instruments","C106794","4ch bidirectional ESD on the PHY side of the magnetics, 0.25 pF, flow-through","1",""

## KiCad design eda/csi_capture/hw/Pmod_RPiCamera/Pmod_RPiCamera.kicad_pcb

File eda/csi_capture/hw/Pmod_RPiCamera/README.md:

# Pmod RPi Camera (Rev. A)

Raspberry Pi カメラ (15 ピン 1.0 mm FFC, 2 レーン MIPI CSI-2) を Pmod 1 個につなぐ変換基板。
FPGA 側はソフト D-PHY (`eda/csi_capture`, `rtl/csi2`)。KiCad 10。

状態: **設計のみ (未発注・実機未確認)**。ERC / DRC (回路図との一致を含む) はエラー 0。

## 仕様

- 外形 25.4 × 24.13 mm、2 層 1.6 mm (FR4)、角 1.27 mm 面取り。
  FFC コネクタ (取付金具込み 20.8 mm) を載せるため Pmod 標準幅 (20.32 mm) より片側 2.5 mm 程度広い
- J1: Pmod 2x6 直角ヘッダ (TangFPGAExtensions の `Conn_Pmod_Spec_B_Thin`)、基板下端
- J2: **Amphenol (FCI) SFW15R-1STE1LF** (15 ピン 1.0 mm FFC、**下面接点**、ZIF、JLC C3168538)。
  Raspberry Pi Camera Module 2 の J1 と同じ部品。フットプリントは FCI 図面 JSA95855 rev AE / JSA95854
  から作成 (`Local/local.pretty`)。基板上端寄り、ケーブルは上から挿す (ハウジング前端は基板端から 2.5 mm 内側)。
  rev A の当初は TE 1-84952-5 だったが JLC 在庫が 1 個のため変更 (接点列の位置は同じ = 配線は無変更)
- CSI 3 対: 差動 100Ω (Pmod_DisplayPort と同じ Link クラス 0.1661 / 0.127 mm)、
  F.Cu のみ・ビアなし、B.Cu は全面 GND (3.3V の短いストラップは I2C の下だけ)。
  P/N の長さ差 ~2.5 mm (~17 ps) は 1 Gbps 以下では無視できる
- F1: ポリスイッチ 0.5 A (カメラの 3.3V)、C1: 10 µF、R1/R2: I2C プルアップ 2.2k、R3: CAM_GPIO プルアップ 10k
- 直列抵抗・AC 結合・バイアス抵抗なし (D-PHY は DC 結合が必須、終端は FPGA 内蔵)

## ピン割り当て

| Pmod | 信号 | FFC | Tang Primer 25K (pmod0) |
|---|---|---|---|
| 1 / 7 | SCL / SDA | 13 / 14 | F5 / G5 |
| 2 / 8 | CLK P / N | 9 / 8 | G7 / G8 |
| 3 / 9 | D1 P / N | 6 / 5 | H8 / H7 |
| 4 / 10 | D0 P / N | 3 / 2 | H5 / J5 |
| 5, 11 | GND | 1, 4, 7, 10, MP | |
| 6, 12 | 3.3 V | 15 (F1 経由) | |
| — | CAM_GPIO | 11 | R3 で 3.3 V へ (カメラは Pmod 給電で即起動) |
| — | CAM_CLK | 12 | 未接続 |

FFC のピン配置は Raspberry Pi 4 公式回路図 (J3 CAMERA) で確認。Pmod 上の並び (CLK, D1, D0) は
FFC 上の並びと同じ順にして、差動対が交差しないようにしてある (FPGA の `pins.cst` も同じ割り当て)。
FPGA 側の定義は `mod/pmod_rpi_camera/pmod_pins.csv`。

## 使えるカメラ

- Raspberry Pi Camera Module 2 (IMX219) と社外の IMX219 モジュール (24 MHz 水晶): `eda/csi_capture`
- Digilent Pcam 5C (OV5640): `eda/csi_capture_pcam5c`。**rev A で受信確認済み** (2026-11-16、280 Mbps × 2 で誤り 0)。Raspberry Pi カメラとピン互換で、カメラ側コネクタも
  基板側に接点。付属ケーブル (両端で接点の向きが逆) でピン n ↔ ピン n。11 番 PWUP は R3 で常時 ON
- Camera Module 3 (IMX708): 基板は使えるが初期化 ROM が未作成

## ケーブルの向き

公式資料から確認済み:
- 標準カメラケーブル (Raspberry Pi RP-008146) は**両端で接点の面が逆** (片端は上面、もう片端は下面)
- カメラ側 J1 (SFW15R-1STE1LF) も本基板の J2 も**下面接点で、ピン 1 の位置の約束が同じ**
  (FCI JSA95855: 実装面から見て、ケーブル挿入口を手前にしたときピン 1 が左)

同じコネクタ同士を両端逆面のケーブルでつなぐと、基板の向きによらず **ピン n ↔ ピン n** になる
(3.3V は 15 番どうし、GND は 1 番どうし)。カメラに付属の標準ケーブルを使うこと。
**両端が同じ面の社外ケーブル**では逆転し、本基板の 3.3V (15 番) がカメラの GND に当たる (F1 が制限する)。

念のための確認 (カメラをつながずに): ケーブルを J2 に挿し、ケーブル反対端の導体 1 番と Pmod の GND (5/11 番) の
導通をテスタで見る。導通すれば正しい。

## 製造データ

`tools/build.sh` が ERC / DRC (回路図との一致、ベタ再充填込み) を通してから `fab/` を作る:

| ファイル | 内容 |
|---|---|
| `fab/Pmod_RPiCamera_gerber.zip` | ガーバー (F/B Cu, Mask, Silk, F.Paste, Edge) + ドリル (PTH/NPTH 別) |
| `fab/Pmod_RPiCamera_bom.csv` | 部品表 (LCSC 番号、MPN 付き) |
| `fab/Pmod_RPiCamera_pos.csv` | 実装位置 (表面のみ、原点は基板左下) |
| `fab/jlc/Pmod_RPiCamera_jlc_bom.csv`, `..._jlc_cpl.csv` | JLCPCB 実装用 BOM / CPL (LCSC 番号のある部品のみ。J1 は手はんだ想定で除外) |
| `fab/lcsc/Pmod_RPiCamera_lcsc_5pcs.csv` | LCSC 部品購入用 (5 枚分、J1 含む)。`tools/lcsc_order.py N` で N 枚分を作り直す (LCSC に問い合わせて最小発注数・単価・在庫を反映、要ネットワーク) |
| `fab/Pmod_RPiCamera_schematic.pdf` | 回路図 |
| `fab/*.png` | 3D レンダリング |
| `fab/erc.rpt`, `fab/drc.rpt` | 検査結果 (ライブラリ表の警告はヘッドレス環境由来) |

回路図・基板の初版は `tools/gen_sch.py` / `tools/gen_pcb.py` で生成し、その後 KiCad で手を入れている
(rev A: P 側の等長化ミアンダ、ティアドロップ、ロゴ、J2 を SFW15R-1STE1LF に変更、LCSC 番号)。**KiCad のファイルが正**
(スクリプトは初版の TE コネクタのまま)。`tools/build.sh` は既定で
現状のファイルを検査して出力するだけ。`--regen` を付けるとスクリプトから作り直し、KiCad での修正は消える。

## 部品 (JLCPCB 在庫は 2026-10-18 時点)

| Ref | 部品 | LCSC | 備考 |
|---|---|---|---|
| J1 | 2x6 2.54 mm 直角ピンヘッダ | — | 手はんだ想定。JLC で載せるならピン長・本体寸法をフットプリントと照合 (候補 C41417354) |
| J2 | Amphenol SFW15R-1STE1LF | C3168538 | 在庫 9,155、Extended |
| F1 | RUILON SMD0805P050TF (I_hold 0.5 A, 6 V) | C20978 | 代替 Littelfuse 0805L050WR (C207022) |
| C1 | Samsung CL21A106KAYNNNE (10 µF 25 V X5R 0805) | C15850 | Basic |
| R1, R2 | UNI-ROYAL 0402WGF2201TCE (2.2 kΩ) | C25879 | Basic |
| R3 | UNI-ROYAL 0402WGF1002TCE (10 kΩ) | C25744 | Basic |

JLC の配置プレビューで J2 の回転・原点を確認すること (KiCad のフットプリント原点は接点列の中心。
JLC 側のモデル原点と違う場合はオフセットが出る)。J2 の 3D モデルは無い (3D 画像に J2 は写らない)。

## 未確定事項

- 差動インピーダンスは DP 基板の実績値を流用 (2 層 1.6 mm でのペア結合主体)。製造業者のスタックアップで要再計算
- カメラ v2 の消費電流 (~250 mA 程度の見込み、未実測) に対する F1 の定格と電圧降下
- GW5A LVDS25 入力のコモンモード下限 (SLVS-200 は ~200 mV) は FPGA 側の最大リスク (`../../README.md`)

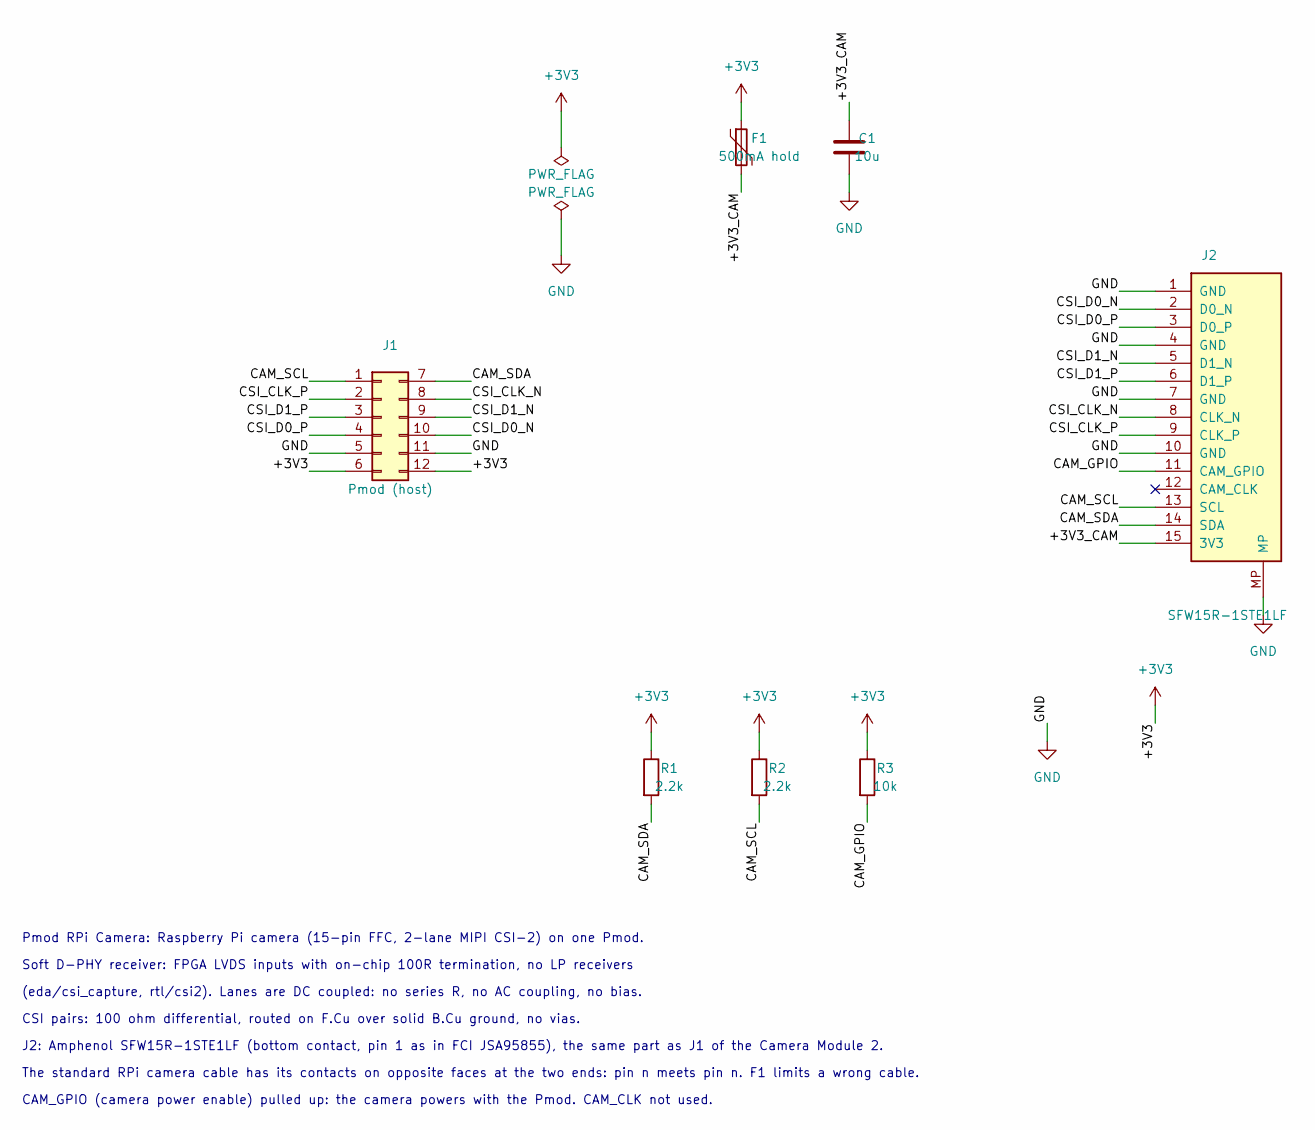
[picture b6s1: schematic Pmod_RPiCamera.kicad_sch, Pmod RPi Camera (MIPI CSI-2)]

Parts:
C1: 10u; C_0805_2012Metric; MPN Samsung CL21A106KAYNNNE; LCSC C15850
F1: 500mA hold; Fuse_0805_2012Metric; MPN RUILON SMD0805P050TF (alt. Littelfuse 0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; LCSC C20978
J1: Pmod (host); Conn_Pmod_Spec_B_Thin
J2: SFW15R-1STE1LF; Amphenol_SFW15R-1STE1LF_1x15-1MP_P1.0mm_Horizontal; MPN Amphenol ICC (FCI) SFW15R-1STE1LF; LCSC C3168538
R1, R2: 2.2k; R_0402_1005Metric; MPN UNI-ROYAL 0402WGF2201TCE; LCSC C25879
R3: 10k; R_0402_1005Metric; MPN UNI-ROYAL 0402WGF1002TCE; LCSC C25744

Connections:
+3V3: F1.1, J1.6, J1.12, R1.1, R2.1, R3.1
/+3V3_CAM: C1.1, F1.2, J2.15 (3V3)
/CAM_GPIO: J2.11 (CAM_GPIO), R3.2
/CAM_SCL: J1.1, J2.13 (SCL), R2.2
/CAM_SDA: J1.7, J2.14 (SDA), R1.2
/CSI_CLK_N: J1.8, J2.8 (CLK_N)
/CSI_CLK_P: J1.2, J2.9 (CLK_P)
/CSI_D0_N: J1.10, J2.2 (D0_N)
/CSI_D0_P: J1.4, J2.3 (D0_P)
/CSI_D1_N: J1.9, J2.5 (D1_N)
/CSI_D1_P: J1.3, J2.6 (D1_P)
GND: C1.2, J1.5, J1.11, J2.1 (GND), J2.4 (GND), J2.7 (GND), J2.10 (GND), J2.MP

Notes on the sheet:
CAM_GPIO (camera power enable) pulled up: the camera powers with the Pmod. CAM_CLK not used.
Pmod RPi Camera: Raspberry Pi camera (15-pin FFC, 2-lane MIPI CSI-2) on one Pmod.
CSI pairs: 100 ohm differential, routed on F.Cu over solid B.Cu ground, no vias.
(eda/csi_capture, rtl/csi2). Lanes are DC coupled: no series R, no AC coupling, no bias.
Soft D-PHY receiver: FPGA LVDS inputs with on-chip 100R termination, no LP receivers
The standard RPi camera cable has its contacts on opposite faces at the two ends: pin n meets pin n. F1 limits a wrong cable.
J2: Amphenol SFW15R-1STE1LF (bottom contact, pin 1 as in FCI JSA95855), the same part as J1 of the Camera Module 2.

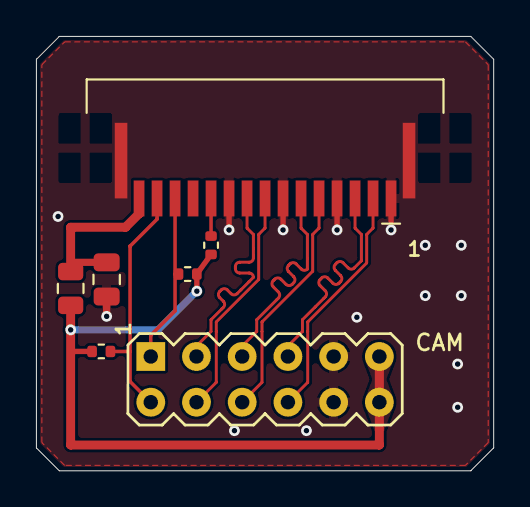
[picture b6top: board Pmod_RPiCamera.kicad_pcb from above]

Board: 2 copper layers, 25.4 x 24.1 mm, 8 parts (1 on the bottom side), 12 nets.

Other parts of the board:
LOGO1: logo

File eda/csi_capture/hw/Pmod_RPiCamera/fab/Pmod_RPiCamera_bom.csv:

"Reference","Value","Footprint","QUANTITY","LCSC","MPN","Description"
"C1","10u","Capacitor_SMD:C_0805_2012Metric","1","C15850","Samsung CL21A106KAYNNNE","10 uF 25 V X5R 0805"
"F1","500mA hold","Fuse:Fuse_0805_2012Metric","1","C20978","RUILON SMD0805P050TF (alt. Littelfuse 0805L050WR, C207022)","Resettable fuse, 6 V, I_hold 0.5 A, 0805"
"J1","Pmod (host)","local:Conn_Pmod_Spec_B_Thin","1","","","Pmod 2x6 right angle (Digilent Pmod Type 1A / spec B)"
"J2","SFW15R-1STE1LF","local:Amphenol_SFW15R-1STE1LF_1x15-1MP_P1.0mm_Horizontal","1","C3168538","Amphenol ICC (FCI) SFW15R-1STE1LF","15-pin 1.0 mm FFC ZIF, bottom contact; the connector of the Raspberry Pi Camera Module 2 itself"
"R1,R2","2.2k","Resistor_SMD:R_0402_1005Metric","2","C25879","UNI-ROYAL 0402WGF2201TCE","2.2k 1% 0402"
"R3","10k","Resistor_SMD:R_0402_1005Metric","1","C25744","UNI-ROYAL 0402WGF1002TCE","10k 1% 0402"

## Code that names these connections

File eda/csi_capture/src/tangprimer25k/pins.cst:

// Tang Primer 25K — MIPI CSI-2 camera adapter on pmod0 (bank 1).
//
// Adapter: hw/Pmod_RPiCamera (Pmod 12-pin -> Raspberry Pi 15-pin FFC):
//   Pmod 1 / 7  = SCL / SDA   (FFC 13 / 14), 2.2k pull-ups to 3.3 V
//   Pmod 2 / 8  = CLK P / N   (FFC 9 / 8)
//   Pmod 3 / 9  = D1  P / N   (FFC 6 / 5)
//   Pmod 4 / 10 = D0  P / N   (FFC 3 / 2)
// (the order on the Pmod follows the FFC's, so the board's pairs never
//  cross; the clock lane is oversampled like a data lane, any pin will do)
//   Pmod 5, 11 = GND, 6, 12 = 3.3 V (FFC 15; FFC 11 CAM_GPIO pulled up)
// Pmod pin N / N+6 are the board's differential pairs; the N pins are
// placed by the tool. All four pairs of this slot are in bank 1, the only
// Pmod bank with on-chip 100 ohm termination on every pair (bank 6 has
// none) and the bank whose HCLK the PLL_T 4-phase clocks reach
// (eda/easycdr_trace pins_usb.cst uses the same slot for its OSIDES32).
// The termination stays on: D-PHY LP-11 puts 1.2 V on both wires (no
// current), LP-01 / LP-00 only appear briefly before HS.
IO_LOC "csi_clk_p" G7,G8;
IO_PORT "csi_clk_p" IO_TYPE=LVDS25 PULL_MODE=NONE DIFF_RESISTOR=ON BANK_VCCIO=3.3;
IO_LOC "csi_d0_p" H5,J5;
IO_PORT "csi_d0_p" IO_TYPE=LVDS25 PULL_MODE=NONE DIFF_RESISTOR=ON BANK_VCCIO=3.3;
IO_LOC "csi_d1_p" H8,H7;
IO_PORT "csi_d1_p" IO_TYPE=LVDS25 PULL_MODE=NONE DIFF_RESISTOR=ON BANK_VCCIO=3.3;

// I2C: open drain by the IOBUF alone (I = 0, OEN = release). With
// OPEN_DRAIN=ON on top of that, both lines read low all the time on the
// hardware (every address ACKed, every read 0x00).
IO_LOC "cam_scl" F5;
IO_PORT "cam_scl" IO_TYPE=LVCMOS33 PULL_MODE=UP DRIVE=8;
IO_LOC "cam_sda" G5;
IO_PORT "cam_sda" IO_TYPE=LVCMOS33 PULL_MODE=UP DRIVE=8;

INS_LOC "u_phy/u_pll_rx/PLLA_inst" PLL_T;

IO_LOC "clock" E2;
IO_PORT "clock" IO_TYPE=LVCMOS33 PULL_MODE=NONE;
IO_LOC "reset_button" H11;
IO_PORT "reset_button" IO_TYPE=LVCMOS33 PULL_MODE=DOWN;

// USB-UART (USB Debugger, FT2232 if01), 115200 8N1
IO_LOC "uart_txd" C3;
IO_PORT "uart_txd" IO_TYPE=LVCMOS33 PULL_MODE=NONE DRIVE=8;
IO_LOC "uart_rxd" B3;
IO_PORT "uart_rxd" IO_TYPE=LVCMOS33 PULL_MODE=UP;

IO_LOC "led_rx" B2;
IO_PORT "led_rx" IO_TYPE=LVCMOS33 PULL_MODE=NONE DRIVE=8;
IO_LOC "led_err" C2;
IO_PORT "led_err" IO_TYPE=LVCMOS33 PULL_MODE=NONE DRIVE=8;

// scope taps: pmod2 bottom row (pmod2_7..10)
IO_LOC "dbg[0]" G10;
IO_PORT "dbg[0]" IO_TYPE=LVCMOS33 PULL_MODE=NONE DRIVE=8;
IO_LOC "dbg[1]" D10;
IO_PORT "dbg[1]" IO_TYPE=LVCMOS33 PULL_MODE=NONE DRIVE=8;
IO_LOC "dbg[2]" B10;
IO_PORT "dbg[2]" IO_TYPE=LVCMOS33 PULL_MODE=NONE DRIVE=8;
IO_LOC "dbg[3]" C10;
IO_PORT "dbg[3]" IO_TYPE=LVCMOS33 PULL_MODE=NONE DRIVE=8;
